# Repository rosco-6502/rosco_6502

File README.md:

# Really Old-School Computer - 6502

## A 65C02 Single-Board Computer

This repository holds design files, firmware and software for the Really Old-School Computer
(6502) single-board computer, AKA the rosco_6502. This is a fully-featured, programmable,
extensible and capable 8-bit retro computer that is completely open source  and will be
available in kit form (coming soon).

The rosco_6502 is the "little brother" of the popular [rosco_m68k](https://github.com/rosco-m68k)
m68k computer. It is made by the same people, and shares the ethos of being powerful, extensible
and above all, fun.

This project contains all the design files and source code for the project.

* All Software released under the MIT licence. See LICENSE for details.
* All Hardware released under the CERN Open Hardware licence.See LICENCE.hardware.txt.
* All Documentation released under Creative Commons Attribution. See <https://creativecommons.org/licenses/by/2.0/uk/>

## Specifications

### Hardware

The hardware specifications for the rosco_6502 are:

* WDC 65C02 at up-to 14MHz (In theory, 10MHz testing target currently).
* XR68C681P provides two UARTs, Timers and SD Card / SPI / GPIO
* 528KB RAM
  * 16KB low RAM ($0000 - $3FFF)
  * 16 x 32KB RAM banks ($4000 - $BFFF)
* 8KB IO space ($C000 - $DFFF)
* 8KB or 32KB (banked) ROM $E000 - $FFFF
* High-speed decode and glue logic handled by Atmel F22V10C PLDs.
* Comprehensive expansion and IO connectors allow the system to be easily expanded!

You can see the electrical designs in [kicad](design/kicad). Programmable logic lives in [pld](code/pld).

### Software

The board design is proven and working well, and work is underway on
initial bringup code and user ROM. Currently, this means the board can
boot, initialize hardware, and drop into [WozMon](http://jefftranter.blogspot.com/2012/05/woz-mon.html)
allowing programs to be keyed in (slowly!) or pasted-to-terminal
for running on the board.

You can see the code that's being used for this in the [firstboot](code/firmware/firstboot)
directory. This is also where the banked ROM layout is being developed.

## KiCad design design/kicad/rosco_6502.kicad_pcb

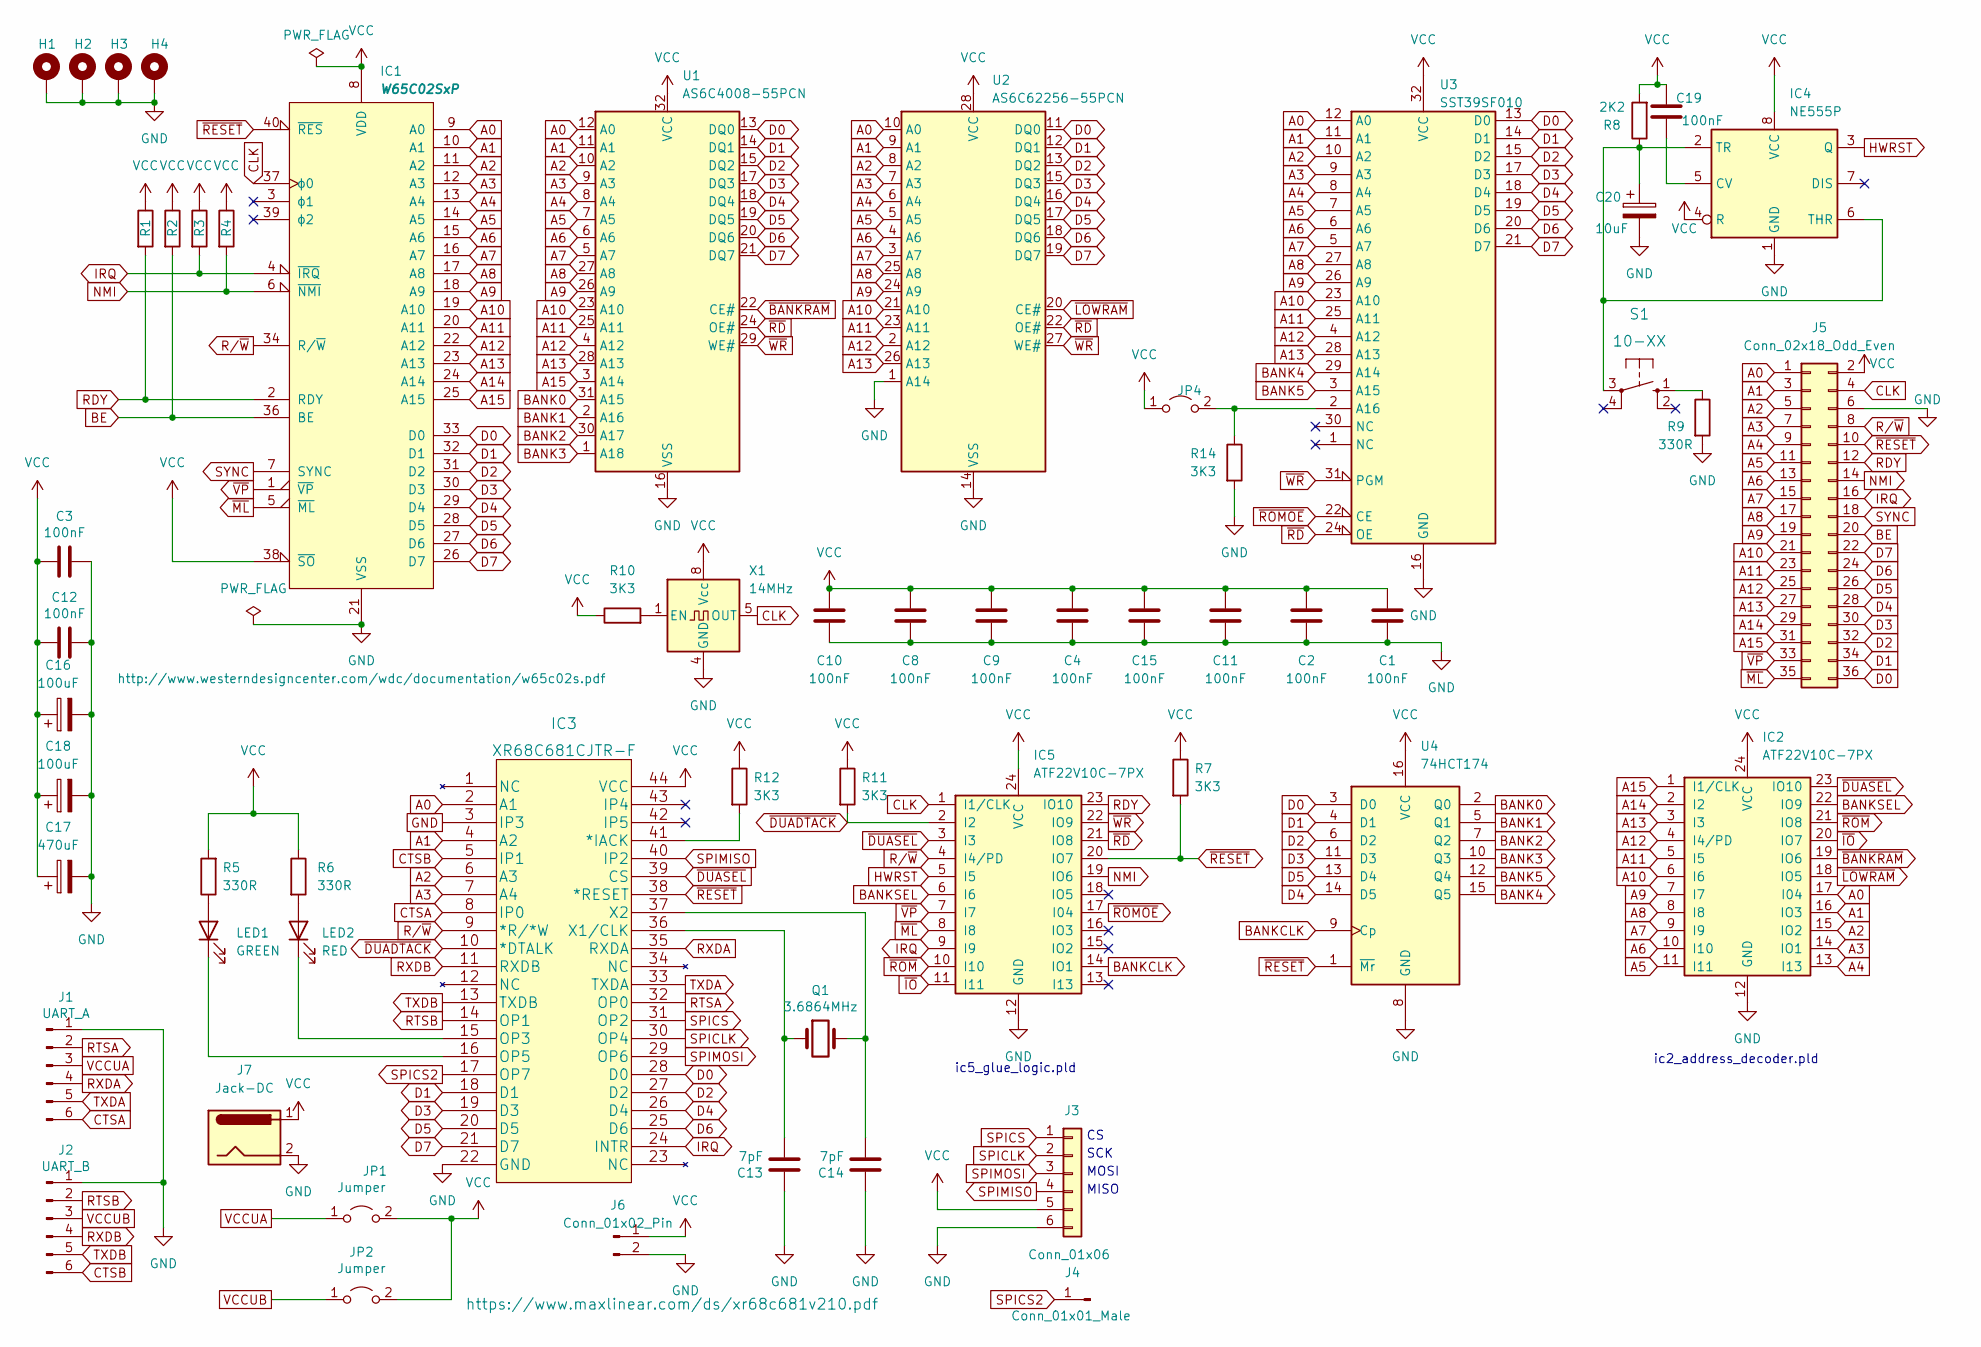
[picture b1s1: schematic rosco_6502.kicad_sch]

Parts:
C1, C2, C3, C4, C8, C9, C10, C11, C12, C15, C19: 100nF; C_Rect_L4.0mm_W2.5mm_P2.50mm
C13, C14: 7pF; C2.5_or_3.5-3
C16, C18: 100uF; CP_Radial_D6.3mm_P2.50mm
C17: 470uF; CP_Radial_D7.5mm_P2.50mm
C20: 10uF; CP_Radial_D6.3mm_P2.50mm
H1, H2, H3, H4: MountingHole_Pad; MountingHole_3.5mm_Pad
IC1: W65C02SxP; DIP-40_W15.24mm_Socket_LongPads
IC2, IC5: ATF22V10C-7PX; DIP-24_W7.62mm_Socket_LongPads
IC3: XR68C681CJTR-F; PLCC-44_THT-Socket
IC4: NE555P; DIP-8_W7.62mm
J1: UART_A; PinHeader_1x06_P2.54mm_Vertical
J2: UART_B; PinHeader_1x06_P2.54mm_Vertical
J3: Conn_01x06; PinHeader_1x06_P2.54mm_Vertical
J4: Conn_01x01_Male; PinHeader_1x01_P2.54mm_Vertical
J5: Conn_02x18_Odd_Even; PinHeader_2x18_P2.54mm_Vertical
J6: Conn_01x02_Pin; PinHeader_1x02_P2.54mm_Vertical
J7: Jack-DC; BarrelJack_Horizontal
JP1, JP2: Jumper; PinHeader_1x02_P2.54mm_Vertical
JP4: Conn_02x02_Odd_Even; PinHeader_1x02_P2.54mm_Vertical
LED1: GREEN; LED_D5.0mm
LED2: RED; LED_D5.0mm
Q1: 3.6864MHz; Crystal_HC49-4H_Vertical
R1, R2, R3, R4, R7, R10, R11, R12, R14: 3K3; R_Axial_DIN0207_L6.3mm_D2.5mm_P10.16mm_Horizontal
R5, R6, R9: 330R; R_Axial_DIN0207_L6.3mm_D2.5mm_P10.16mm_Horizontal
R8: 2K2; R_Axial_DIN0207_L6.3mm_D2.5mm_P10.16mm_Horizontal
S1: 10-XX; B3F-10XX
U1: AS6C4008-55PCN; DIP-32_W15.24mm_Socket_LongPads
U2: AS6C62256-55PCN; DIP-28_W15.24mm_Socket_LongPads
U3: SST39SF010; DIP-32_W15.24mm_Socket_LongPads
U4: 74HCT174; DIP-16_W7.62mm_Socket_LongPads
X1: 14MHz; Oscillator_DIP-8

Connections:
A0: IC1.9 (A0), IC2.17 (I04), IC3.2 (A1), J5.1, U1.12 (A0), U2.10 (A0), U3.12 (A0)
A1: IC1.10 (A1), IC2.16 (IO3), IC3.4 (A2), J5.3, U1.11 (A1), U2.9 (A1), U3.11 (A1)
A2: IC1.11 (A2), IC2.15 (IO2), IC3.6 (A3), J5.5, U1.10 (A2), U2.8 (A2), U3.10 (A2)
A3: IC1.12 (A3), IC2.14 (IO1), IC3.7 (A4), J5.7, U1.9 (A3), U2.7 (A3), U3.9 (A3)
A4: IC1.13 (A4), IC2.13 (I13), J5.9, U1.8 (A4), U2.6 (A4), U3.8 (A4)
A5: IC1.14 (A5), IC2.11 (I11), J5.11, U1.7 (A5), U2.5 (A5), U3.7 (A5)
A6: IC1.15 (A6), IC2.10 (I10), J5.13, U1.6 (A6), U2.4 (A6), U3.6 (A6)
A7: IC1.16 (A7), IC2.9 (I9), J5.15, U1.5 (A7), U2.3 (A7), U3.5 (A7)
A8: IC1.17 (A8), IC2.8 (I8), J5.17, U1.27 (A8), U2.25 (A8), U3.27 (A8)
A9: IC1.18 (A9), IC2.7 (I7), J5.19, U1.26 (A9), U2.24 (A9), U3.26 (A9)
A10: IC1.19 (A10), IC2.6 (I6), J5.21, U1.23 (A10), U2.21 (A10), U3.23 (A10)
A11: IC1.20 (A11), IC2.5 (I5), J5.23, U1.25 (A11), U2.23 (A11), U3.25 (A11)
A12: IC1.22 (A12), IC2.4 (I4/PD), J5.25, U1.4 (A12), U2.2 (A12), U3.4 (A12)
A13: IC1.23 (A13), IC2.3 (I3), J5.27, U1.28 (A13), U2.26 (A13), U3.28 (A13)
A14: IC1.24 (A14), IC2.2 (I2), J5.29
A15: IC1.25 (A15), IC2.1 (I1/CLK), J5.31, U1.3 (A14)
BANK0: U1.31 (A15), U4.2 (Q0)
BANK1: U1.2 (A16), U4.5 (Q1)
BANK2: U1.30 (A17), U4.7 (Q2)
BANK3: U1.1 (A18), U4.10 (Q3)
BANK4: U3.29 (A14), U4.15 (Q5)
BANK5: U3.3 (A15), U4.12 (Q4)
BANKCLK: IC5.14 (IO1), U4.9 (Cp)
BANKSEL: IC2.22 (IO9), IC5.6 (I6)
BE: IC1.36 (BE), J5.20, R2.2
CLK: IC1.37 (ϕ0), IC5.1 (I1/CLK), J5.4, X1.5 (OUT)
CTSA: IC3.8 (IP0), J1.6
CTSB: IC3.5 (IP1), J2.6
D0: IC1.33 (D0), IC3.28 (D0), J5.36, U1.13 (DQ0), U2.11 (DQ0), U3.13 (D0), U4.3 (D0)
D1: IC1.32 (D1), IC3.18 (D1), J5.34, U1.14 (DQ1), U2.12 (DQ1), U3.14 (D1), U4.4 (D1)
D2: IC1.31 (D2), IC3.27 (D2), J5.32, U1.15 (DQ2), U2.13 (DQ2), U3.15 (D2), U4.6 (D2)
D3: IC1.30 (D3), IC3.19 (D3), J5.30, U1.17 (DQ3), U2.15 (DQ3), U3.17 (D3), U4.11 (D3)
D4: IC1.29 (D4), IC3.26 (D4), J5.28, U1.18 (DQ4), U2.16 (DQ4), U3.18 (D4), U4.14 (D5)
D5: IC1.28 (D5), IC3.20 (D5), J5.26, U1.19 (DQ5), U2.17 (DQ5), U3.19 (D5), U4.13 (D4)
D6: IC1.27 (D6), IC3.25 (D6), J5.24, U1.20 (DQ6), U2.18 (DQ6), U3.20 (D6)
D7: IC1.26 (D7), IC3.21 (D7), J5.22, U1.21 (DQ7), U2.19 (DQ7), U3.21 (D7)
GND: C1.1, C2.1, C3.1, C4.1, C8.1, C9.1, C10.1, C11.1, C12.1, C13.1, C14.1, C15.1, C16.2, C17.2, C18.2, C20.2, H1.1, H2.1, H3.1, H4.1, IC1.21 (VSS), IC2.12 (GND), IC3.3 (IP3), IC3.22 (GND), IC4.1 (GND), IC5.12 (GND), J1.1, J2.1, J3.6, J5.6, J6.2, J7.2, R9.2, R14.2, U1.16 (VSS), U2.1 (A14), U2.14 (VSS), U3.16 (GND), U4.8 (GND), X1.4 (GND)
HWRST: IC4.3 (Q), IC5.5 (I5)
IRQ: IC1.4 (~IRQ), IC3.24 (INTR), IC5.9 (I9), J5.16, R3.2
NMI: IC1.6 (~NMI), IC5.19 (IO6), J5.14, R4.2
unnamed: IC3.41 (*IACK), R12.2
unnamed: IC3.15 (OP3), LED2.1 (K)
unnamed: IC3.16 (OP5), LED1.1 (K)
unnamed: C13.2, IC3.36 (X1/CLK), Q1.1
unnamed: C14.2, IC3.37 (X2), Q1.2
unnamed: C19.2, IC4.5 (CV)
unnamed: C20.1, IC4.2 (TR), IC4.6 (THR), R8.1, S1.3
unnamed: JP4.2 (B), R14.1, U3.2 (A16)
unnamed: LED1.2 (A), R5.1
unnamed: LED2.2 (A), R6.2
unnamed: R9.1, S1.1 (S)
unnamed: R10.2, X1.1 (EN)
RDY: IC1.2 (RDY), IC5.23 (IO10), J5.12, R1.2
RTSA: IC3.32 (OP0), J1.2
RTSB: IC3.14 (OP1), J2.2
RXDA: IC3.35 (RXDA), J1.4
RXDB: IC3.11 (RXDB), J2.4
R/~W: IC1.34 (R/~W), IC3.9 (*R/*W), IC5.4 (I4/PD), J5.8
SPICLK: IC3.30 (OP4), J3.2
SPICS: IC3.31 (OP2), J3.1
SPICS2: IC3.17 (OP7), J4.1
SPIMISO: IC3.40 (IP2), J3.4
SPIMOSI: IC3.29 (OP6), J3.3
SYNC: IC1.7 (SYNC), J5.18
TXDA: IC3.33 (TXDA), J1.5
TXDB: IC3.13 (TXDB), J2.5
VCC: C1.2, C2.2, C3.2, C4.2, C8.2, C9.2, C10.2, C11.2, C12.2, C15.2, C16.1, C17.1, C18.1, C19.1, IC1.8 (VDD), IC1.38 (~SO), IC2.24 (VCC), IC3.44 (VCC), IC4.4 (R), IC4.8 (VCC), IC5.24 (VCC), J3.5, J5.2, J6.1, J7.1, JP1.2 (B), JP2.2 (B), JP4.1 (A), R1.1, R2.1, R3.1, R4.1, R5.2, R6.1, R7.1, R8.2, R10.1, R11.1, R12.1, U1.32 (VCC), U2.28 (VCC), U3.32 (VCC), U4.16 (VCC), X1.8 (Vcc)
VCCUA: J1.3, JP1.1 (A)
VCCUB: J2.3, JP2.1 (A)
~BANKRAM: IC2.19 (IO6), U1.22 (CE#)
~DUADTACK: IC3.10 (*DTALK), IC5.2 (I2), R11.2
~DUASEL: IC2.23 (IO10), IC3.39 (CS), IC5.3 (I3)
~IO: IC2.20 (IO7), IC5.11 (I11)
~LOWRAM: IC2.18 (IO5), U2.20 (CE#)
~ML: IC1.5 (~ML), IC5.8 (I8), J5.35
~RD: IC5.21 (IO8), U1.24 (OE#), U2.22 (OE#), U3.24 (OE)
~RESET: IC1.40 (~RES), IC3.38 (*RESET), IC5.20 (IO7), J5.10, R7.2, U4.1 (~Mr)
~ROMOE: IC5.17 (I04), U3.22 (CE)
~ROM: IC2.21 (IO8), IC5.10 (I10)
~VP: IC1.1 (~VP), IC5.7 (I7), J5.33
~WR: IC5.22 (IO9), U1.29 (WE#), U2.27 (WE#), U3.31 (PGM)

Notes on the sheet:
ic5_glue_logic.pld
SCK
ic2_address_decoder.pld
MOSI
MISO

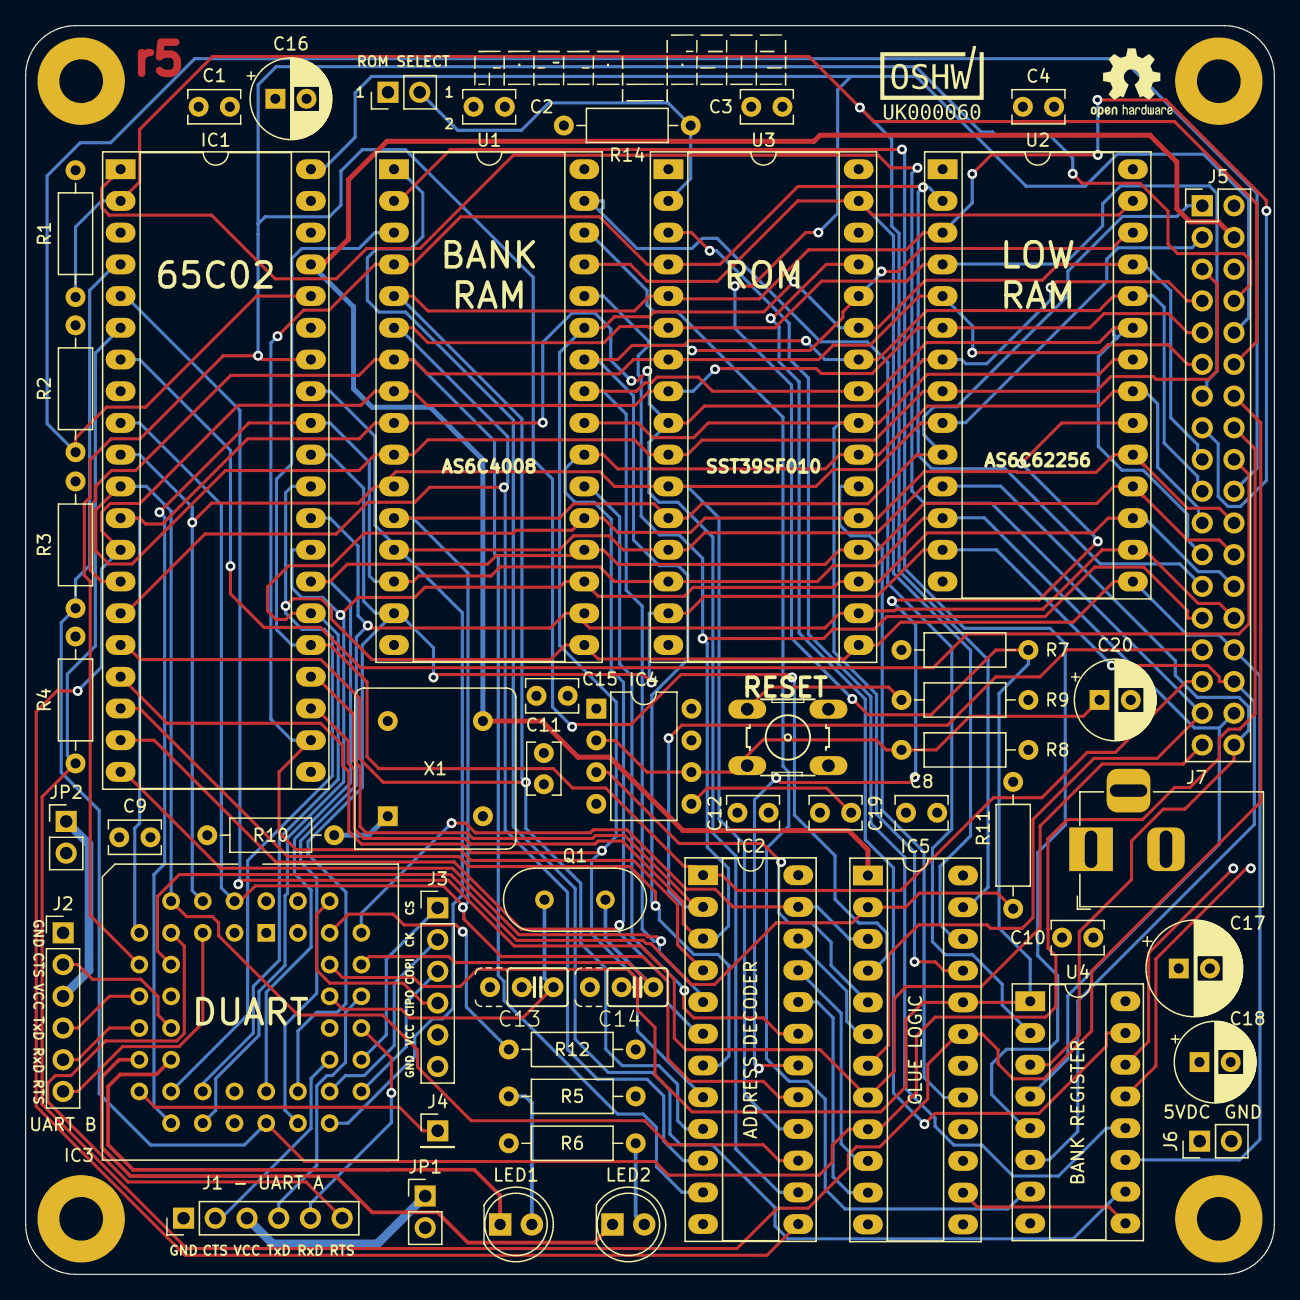
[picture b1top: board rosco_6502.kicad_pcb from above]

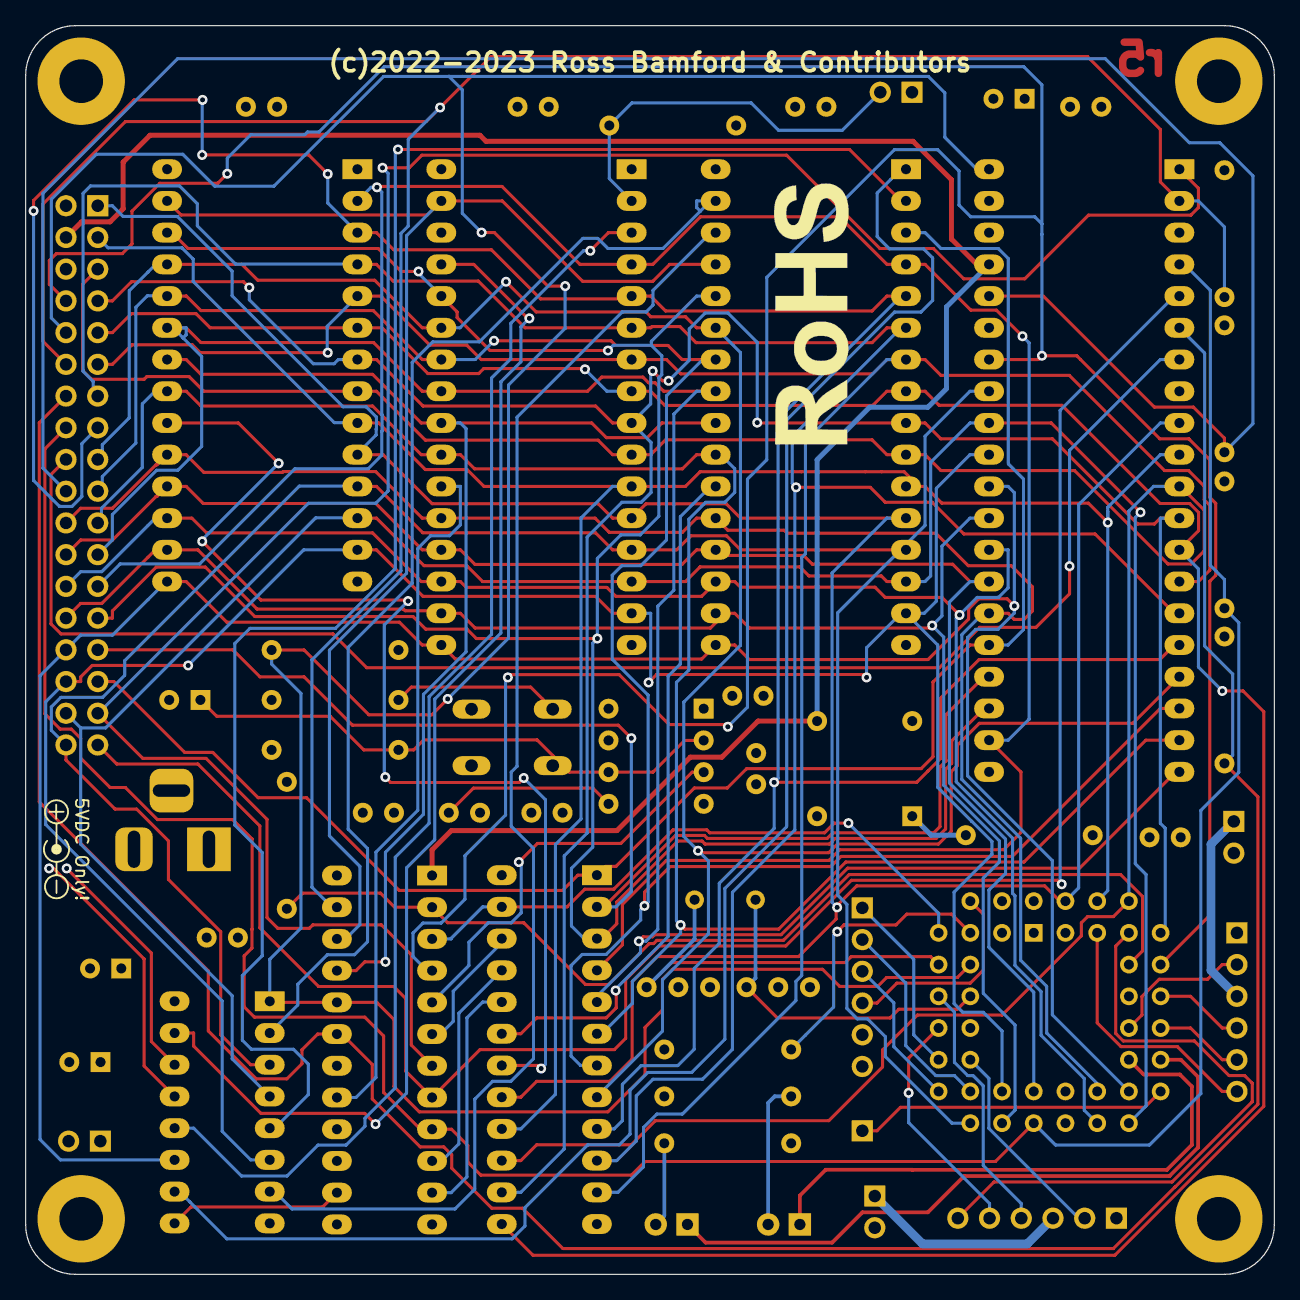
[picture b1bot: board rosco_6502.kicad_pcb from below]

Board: 4 copper layers, 100.0 x 100.0 mm, 63 parts (2 on the bottom side), 81 nets.

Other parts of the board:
OSHWA: LOGO; oshwa
PARITY: Symbol_Barrel_Polarity
ROHS: RoHS-Logo_6mm_SilkScreen
ohw: OSHW-Logo2_7.3x6mm_SilkScreen
rosco6502: rosco_6502

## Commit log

2022-06-18 Initial design & PCB
2022-06-18 Tidy up some tracks
2022-06-18 Power connector & silk update
2022-06-22 Add CLK into RD/WR and reroute
2022-06-22 Add PDF
2022-07-02 Fix DUASEL and add burn scripts
2022-07-02 Fix incorrect 555 hookup
2022-07-02 Fix incorrect button symbol
2022-07-12 Fixes from r0
2022-07-12 Update BOM
2022-07-12 Fix incorrect RDY glue
2022-07-12 First cut bringup code
2022-07-12 Stretch timing for BANKSEL via glue
2022-07-12 Add **very** basic test of bank reg
2022-07-12 Fix PDF
2022-07-13 Proper bankcheck
2022-07-13 Fix higher half of bankram
2022-07-13 Speedier ROM fixes
2022-07-13 Drive ROM OE directly in glue
2022-07-13 Interrupts, currently disabled
2022-07-14 Add missing DUART IACK pullup
2022-07-14 Specifically name all pins, add temp ROMOE for bodge
2022-07-14 Fully working interrupt code
2022-07-25 Make r3 fixes permanent
2022-07-31 Ignore vobj files
2022-07-31 First steps to proper firmware build
2022-08-10 WS for ROM/DUART, working with extra caps
2022-08-17 Remove ROM waitstates
2023-09-09 Remove outdated comment
2023-09-10 Bank ROM
2023-09-10 Fix ROM footprint; README
2023-09-10 Support other ROM as discussed https://discord.com/channels/698525682199822367/1004479727786012803/1005127547442429995
2023-12-02 Update for Kicad 7
2023-12-18 Working, too big
2023-12-18 Make it work and fit
2023-12-18 Fix Y setup bug
2023-12-18 Support banked ROM, do a proper build
2023-12-18 Update LICENSE
2023-12-19 All ROM banks working and switchable
2023-12-19 Only strobe bank register on writes
2023-12-19 wozmon working in all banks
2023-12-20 Tidy up bank checks and increase flash speed
2023-12-20 Tidy up output
2023-12-20 Typo fix
2023-12-20 Toolchain notes
2023-12-29 Add information sheet
2024-03-09 define cleanup, init 2nd UART
2024-03-17 Move bank reg to 0x0 & 0x1
2024-03-17 Switch ROM to SST39SF010
2024-03-17 Fix (?) RDY logic with DUART
2024-03-17 Add OSHWA reg to PCB
2024-03-17 Update for larger ROM mapping
2024-03-17 Decoder update for 1KiB IO
2024-03-17 Fix DUART again
2024-03-18 WIP branch
2024-03-18 brk handler etc.
2024-03-18 cleanup and fixes
2024-03-18 improve irq
2024-03-18 CRLF before run
2024-03-20 WIP working nicely
2024-03-20 boot sysinfo msg
2024-03-21 lots of cleanup and tweaks
2024-03-21 WIP RAM test
2024-03-21 QoL improvements
2024-03-21 Signs of life from SD card test
2024-03-22 minor tweaks and fixes
2024-03-22 SD card initializing properly, WIP
2024-03-23 tweaks
2024-03-23 improvements and smaller cards
2024-03-23 tidy up. Looks like ~30KB/sec-ish
2024-03-23 fixed LED avoiding back to back DUART?
2024-03-24 polish, small benchmark
2024-03-24 init OPCR
2024-03-24 print flag bits
2024-03-25 clean up ZP and add sd_write_block
2024-03-25 cosmetic fixes for hard tabs, trailing whitespace, MD issues
2024-03-25 formatting and cleanup
2024-03-26 cleanup, robustness improvements
2024-03-26 mostly cosmetic changes
2024-03-26 added sd_check_status test
2024-03-26 formatting, comments, consistency
2024-03-26 issue with double init, formatting, comments
2024-03-26 initial super hacky FAT32 test
2024-03-26 allow multiple runs
2024-03-26 test cleanup (kindof), read 2nd file into mem
2024-03-27 directory test
2024-03-27 Initial LFN support and demo/test
2024-03-28 cpu type detect, red led flash on reset, garbage RX on boot
2024-03-28 QoL improvements, message tweaks, Makefile tweak
2024-03-28 remove status cmd and all zeros from OCR causes init
2024-03-28 remove CPU detect, formatting, LED flash
2024-03-28 message tweak
2024-03-28 decimal size print
2024-03-28 finish LFN support, enhance showdir
2024-03-28 also turn on green LED right away
2024-03-28 test larger file
2024-03-30 improve error checking
2024-04-01 initial fat32_openpath
2024-04-04 support smaller FAT32 partitions also
2024-04-04 typo
2024-04-04 test padded "user binary" (starting at $4000)
2024-04-04 move start to $0800
2024-04-04 cleaner fat32 test/example
2024-04-05 fix >64K file reading (~30KB/sec at 10MHz)
2024-04-07 ca65 WIP, 8K builds, but lots of work to do
2024-04-07 fix error codes
2024-04-08 8K booting with ca65 WIP
2024-04-08 update software for new API
2024-04-08 32K banking WIP
2024-04-09 generally back to working state for 8K and 32K
2024-04-10 added READLINE, cleanup
2024-04-12 ca65 software example
2024-04-12 trace tweak
2024-04-12 cleanup pre filesystem
2024-04-12 Makefile cleanup, consistency
2024-04-12 building WIP
2024-04-24 b0rked...
2024-05-06 booting with SD+FAT32 "stubbed" WIP
2024-05-06 Re-add SD card routines
2024-05-06 Re-enable FAT32, get test building. Hits BRK WIP
2024-05-06 Hook FAT vectors up. Showdir now works in fs_test_ca65
2024-05-07 FAT in ROM but not ideal API (yet)
2024-05-07 1st pass at ROSC0DE_6502.BIN file booting from SD
2024-05-08 cleanup, uart flush, assert fixes
2024-05-08 start of menushell utility (WIP, just does dir)
2024-05-08 debugging WIP

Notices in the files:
design/kicad/rosco_6502.kicad_pcb:
Copyright (c)2022-2024 Ross Bamford & Contributors
Open Source Hardware (CERN OHL)
(c)2022-2023 Ross Bamford & Contributors
